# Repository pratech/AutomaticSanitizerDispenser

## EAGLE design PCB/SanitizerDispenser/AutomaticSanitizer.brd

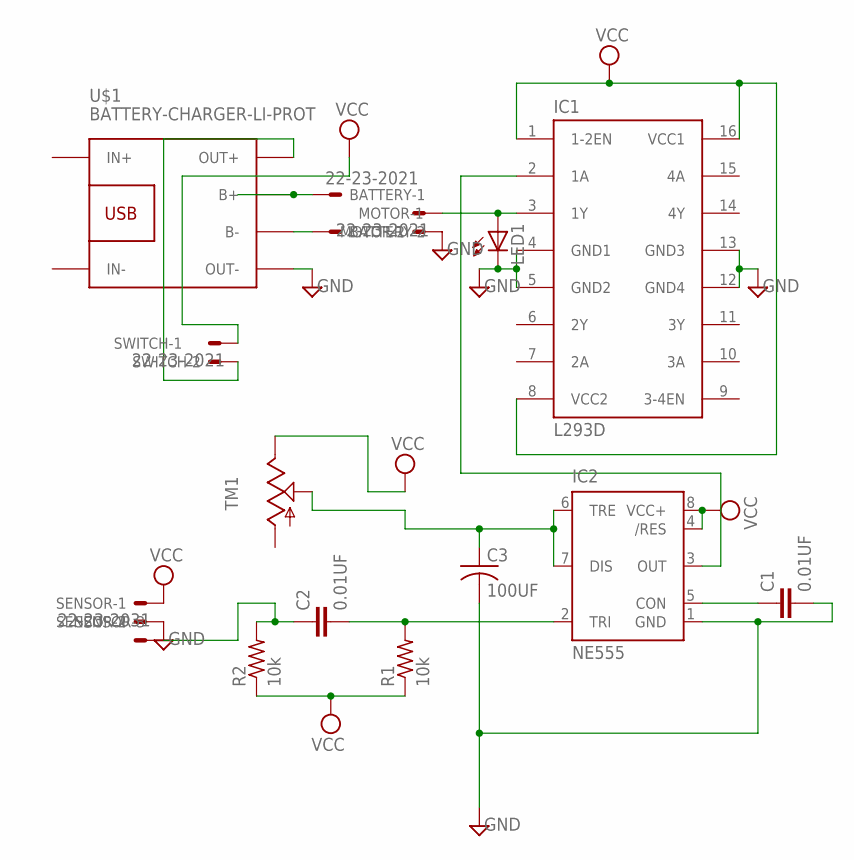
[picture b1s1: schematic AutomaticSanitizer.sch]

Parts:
BATTERY: 22-23-2021
C1, C2: 0.01UF; C2.5-2
C3: 100UF; C025-025X050
IC1: L293D; DIL16
IC2: NE555; DIL-08
LED1: LED5MM
MOTOR: 22-23-2021
R1, R2: 10k; 0204/5
SENSOR: 22-23-2031
SWITCH: 22-23-2021
TM1: TRIM; 6MM
U$1: BATTERY-CHARGER-LI-PROT

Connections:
GND: C1.2, C3.2, IC1.4 (GND1), IC1.5 (GND2), IC1.12 (GND4), IC1.13 (GND3), IC2.1 (GND), LED1.K (C), MOTOR.2, SENSOR.2, U$1.OUT-
unnamed: SWITCH.2, U$1.OUT+
unnamed: C3.1, IC2.6 (TRE), IC2.7 (DIS), TM1.S
unnamed: C1.1, IC2.5 (CON)
unnamed: C2.2, IC2.2 (TRI), R1.2
unnamed: IC1.2 (1A), IC2.3 (OUT)
unnamed: C2.1, R2.2, SENSOR.3
unnamed: BATTERY.1, U$1.B+
unnamed: BATTERY.2, U$1.B-
unnamed: IC1.3 (1Y), LED1.A, MOTOR.1
VCC: IC1.1 (1-2EN), IC1.8 (VCC2), IC1.16 (VCC1), IC2.4 (/RES), IC2.8 (VCC+), R1.1, R2.1, SENSOR.1, SWITCH.1, TM1.E

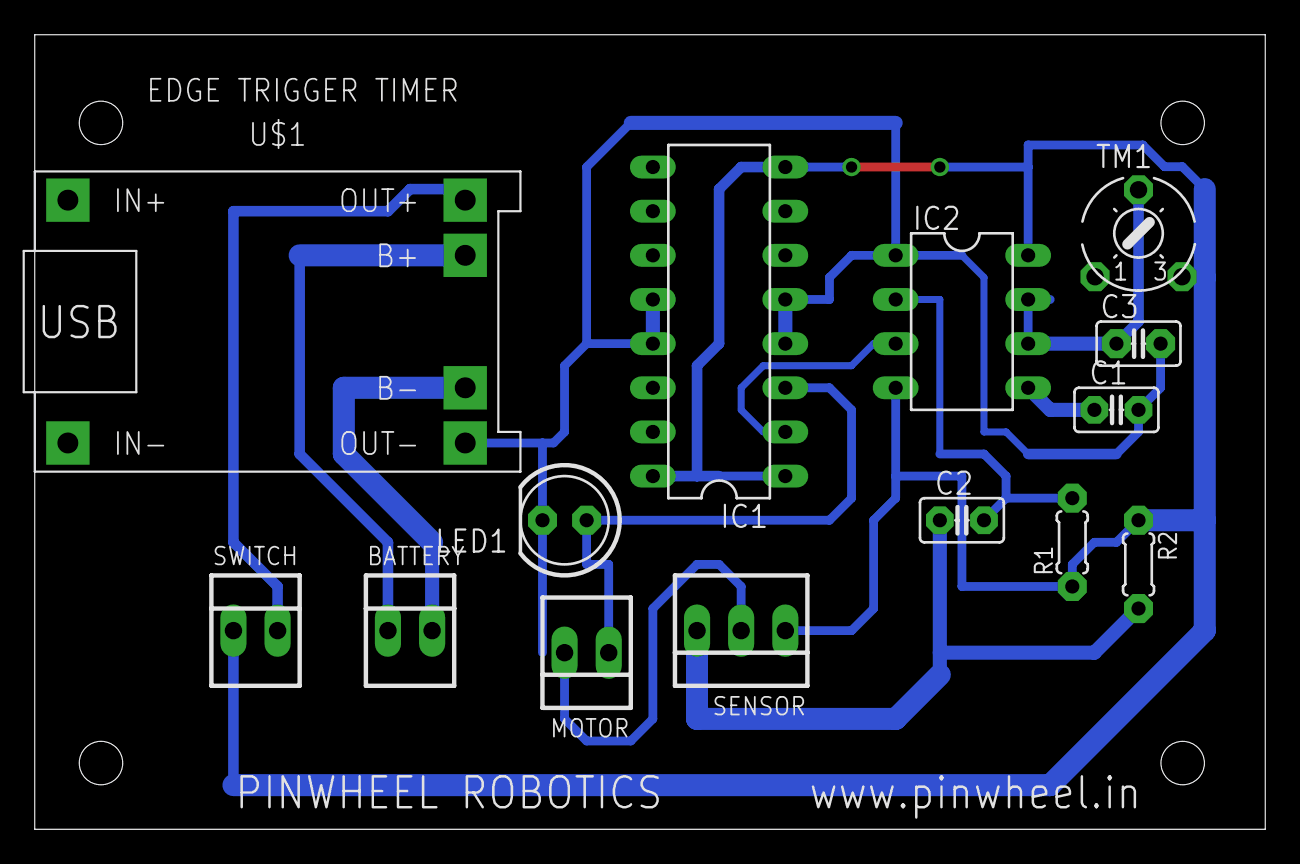
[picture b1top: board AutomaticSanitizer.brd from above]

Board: 2 copper layers, 70.8 x 45.7 mm, 14 parts (0 on the bottom side), 11 nets.

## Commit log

2021-11-28 adding here

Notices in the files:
parts and their libraries:
diy-modules: Released under the Creative Commons Attribution 4.0 International License: http://creativecommons.org/licenses/by/4.0
